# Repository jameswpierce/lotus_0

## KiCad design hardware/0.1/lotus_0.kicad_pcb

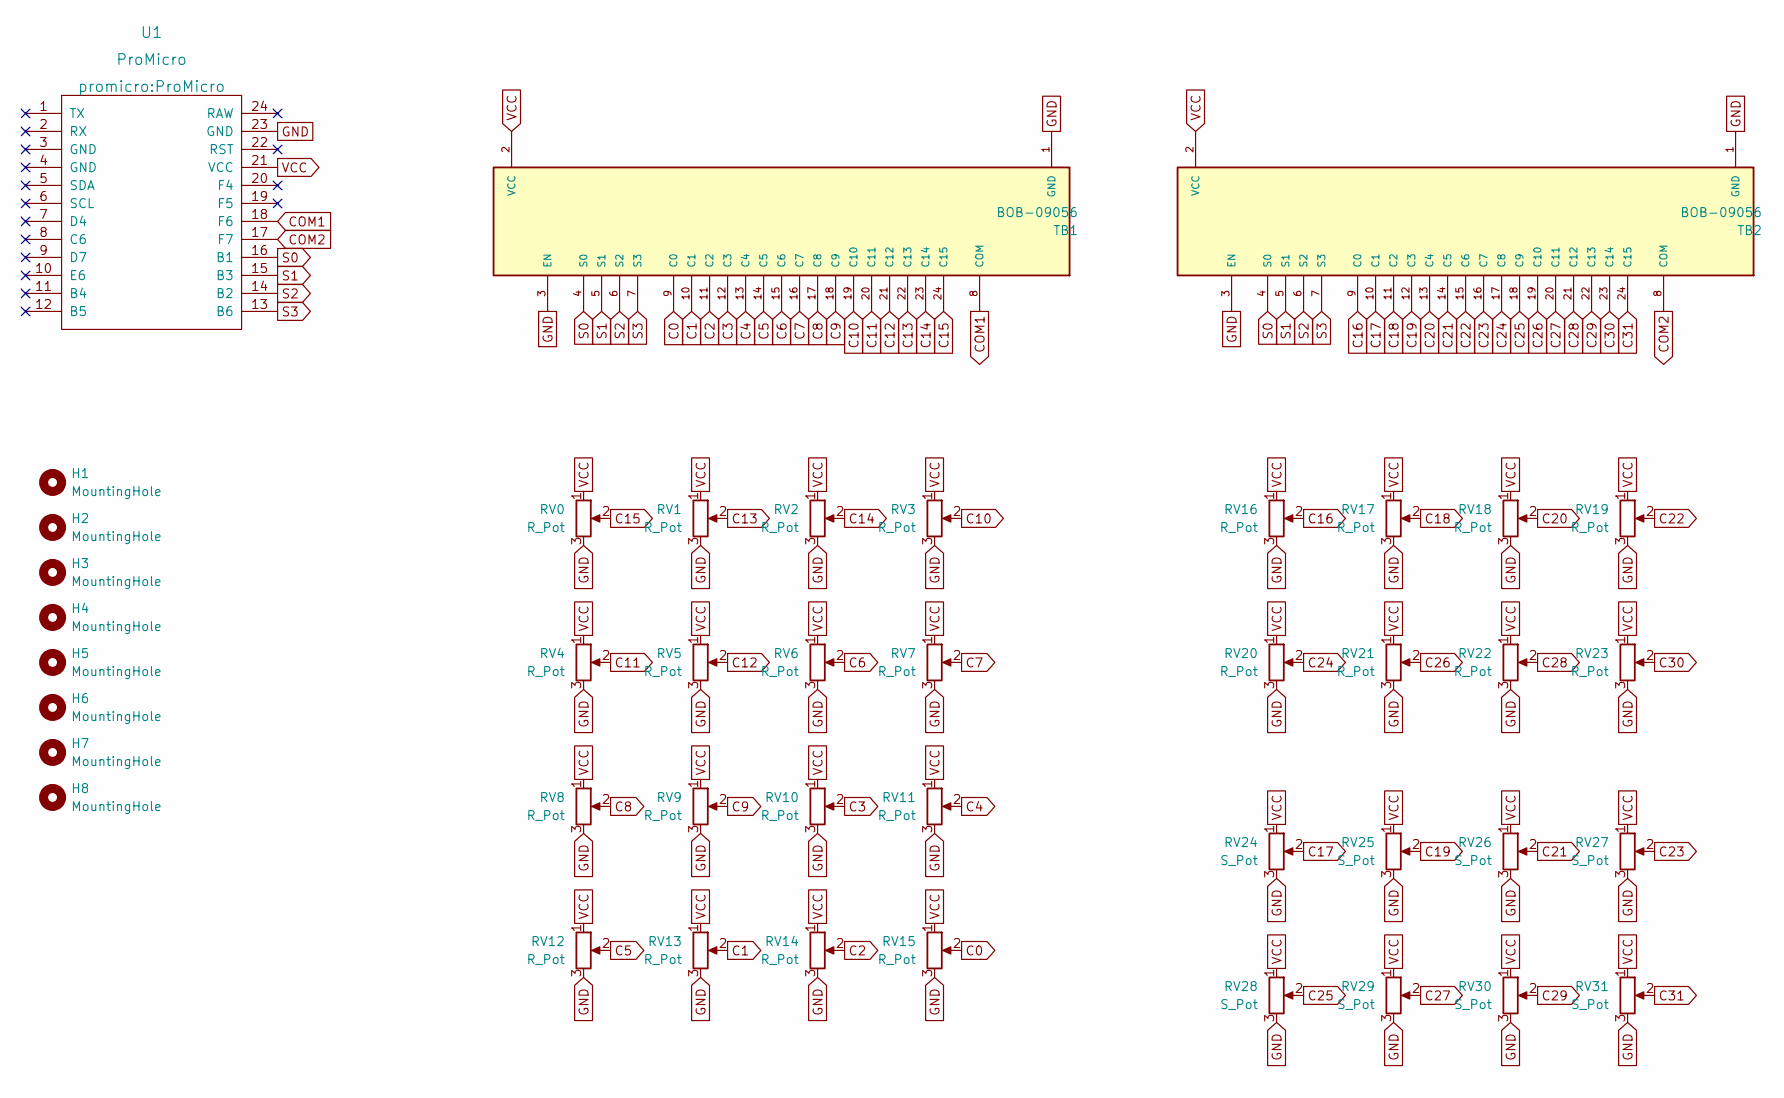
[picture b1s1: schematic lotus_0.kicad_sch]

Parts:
H1, H2, H3, H4, H5, H6, H7, H8: MountingHole; MountingHole_2.2mm_M2_DIN965_Pad
RV0, RV1, RV2, RV3, RV4, RV5, RV6, RV7, RV8, RV9, RV10, RV11, RV12, RV13, RV14, RV15, RV16, RV17, RV18, RV19, RV20, RV21, RV22, RV23: R_Pot; Potentiometer_Bourns_PTV09A-1_Single_Vertical
RV24, RV25, RV26, RV27, RV28, RV29, RV30, RV31: S_Pot; Potentiometer_Bourns_PTA6043_Single_Slide
TB1, TB2: BOB-09056; XDCR_BOB-09056; PARTREV N/A
U1: ProMicro

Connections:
C0: RV15.2, TB1.9 (C0)
C1: RV13.2, TB1.10 (C1)
C2: RV14.2, TB1.11 (C2)
C3: RV10.2, TB1.12 (C3)
C4: RV11.2, TB1.13 (C4)
C5: RV12.2, TB1.14 (C5)
C6: RV6.2, TB1.15 (C6)
C7: RV7.2, TB1.16 (C7)
C8: RV8.2, TB1.17 (C8)
C9: RV9.2, TB1.18 (C9)
C10: RV3.2, TB1.19 (C10)
C11: RV4.2, TB1.20 (C11)
C12: RV5.2, TB1.21 (C12)
C13: RV1.2, TB1.22 (C13)
C14: RV2.2, TB1.23 (C14)
C15: RV0.2, TB1.24 (C15)
C16: RV16.2, TB2.9 (C0)
C17: RV24.2, TB2.10 (C1)
C18: RV17.2, TB2.11 (C2)
C19: RV25.2, TB2.12 (C3)
C20: RV18.2, TB2.13 (C4)
C21: RV26.2, TB2.14 (C5)
C22: RV19.2, TB2.15 (C6)
C23: RV27.2, TB2.16 (C7)
C24: RV20.2, TB2.17 (C8)
C25: RV28.2, TB2.18 (C9)
C26: RV21.2, TB2.19 (C10)
C27: RV29.2, TB2.20 (C11)
C28: RV22.2, TB2.21 (C12)
C29: RV30.2, TB2.22 (C13)
C30: RV23.2, TB2.23 (C14)
C31: RV31.2, TB2.24 (C15)
COM1: TB1.8 (COM), U1.18 (F6)
COM2: TB2.8 (COM), U1.17 (F7)
GND: RV0.3, RV1.3, RV2.3, RV3.3, RV4.3, RV5.3, RV6.3, RV7.3, RV8.3, RV9.3, RV10.3, RV11.3, RV12.3, RV13.3, RV14.3, RV15.3, RV16.3, RV17.3, RV18.3, RV19.3, RV20.3, RV21.3, RV22.3, RV23.3, RV24.3, RV25.3, RV26.3, RV27.3, RV28.3, RV29.3, RV30.3, RV31.3, TB1.1 (GND), TB1.3 (EN), TB2.1 (GND), TB2.3 (EN), U1.23 (GND)
S0: TB1.4 (S0), TB2.4 (S0), U1.16 (B1)
S1: TB1.5 (S1), TB2.5 (S1), U1.15 (B3)
S2: TB1.6 (S2), TB2.6 (S2), U1.14 (B2)
S3: TB1.7 (S3), TB2.7 (S3), U1.13 (B6)
VCC: RV0.1, RV1.1, RV2.1, RV3.1, RV4.1, RV5.1, RV6.1, RV7.1, RV8.1, RV9.1, RV10.1, RV11.1, RV12.1, RV13.1, RV14.1, RV15.1, RV16.1, RV17.1, RV18.1, RV19.1, RV20.1, RV21.1, RV22.1, RV23.1, RV24.1, RV25.1, RV26.1, RV27.1, RV28.1, RV29.1, RV30.1, RV31.1, TB1.2 (VCC), TB2.2 (VCC), U1.21 (VCC)

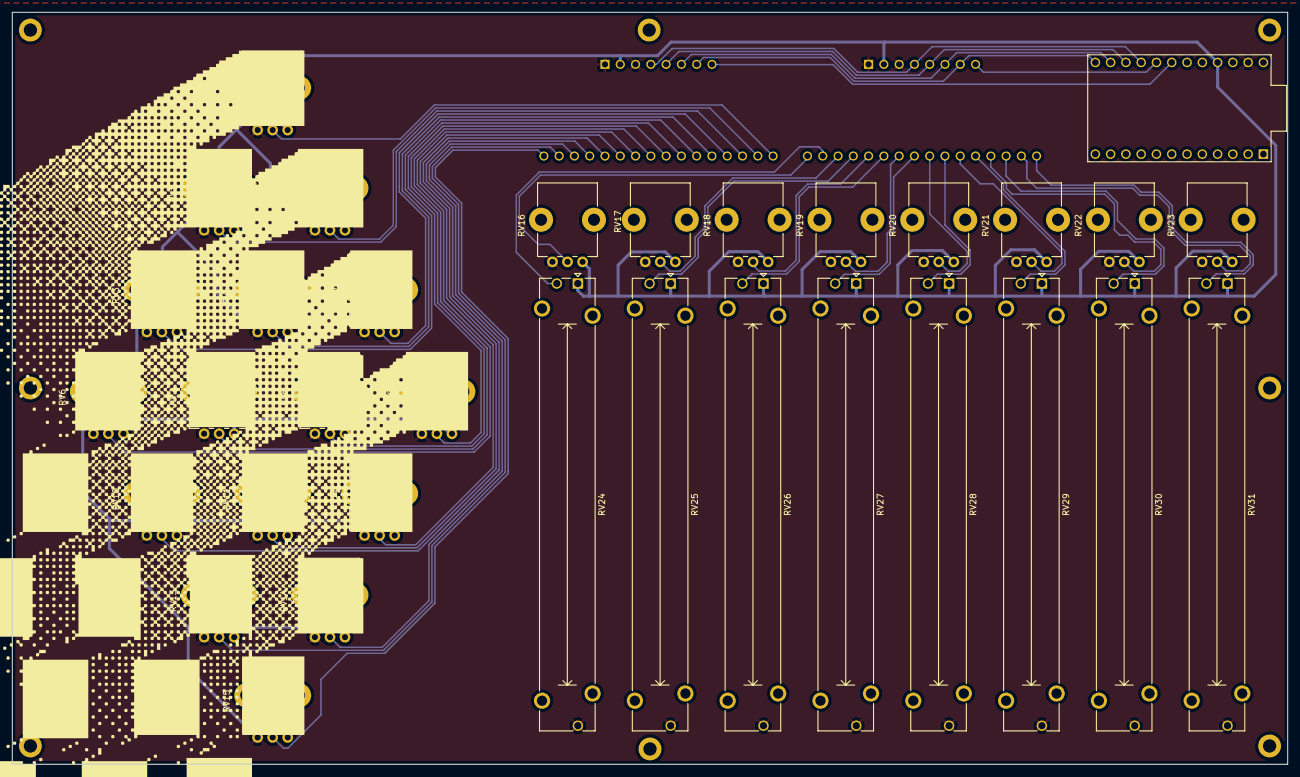
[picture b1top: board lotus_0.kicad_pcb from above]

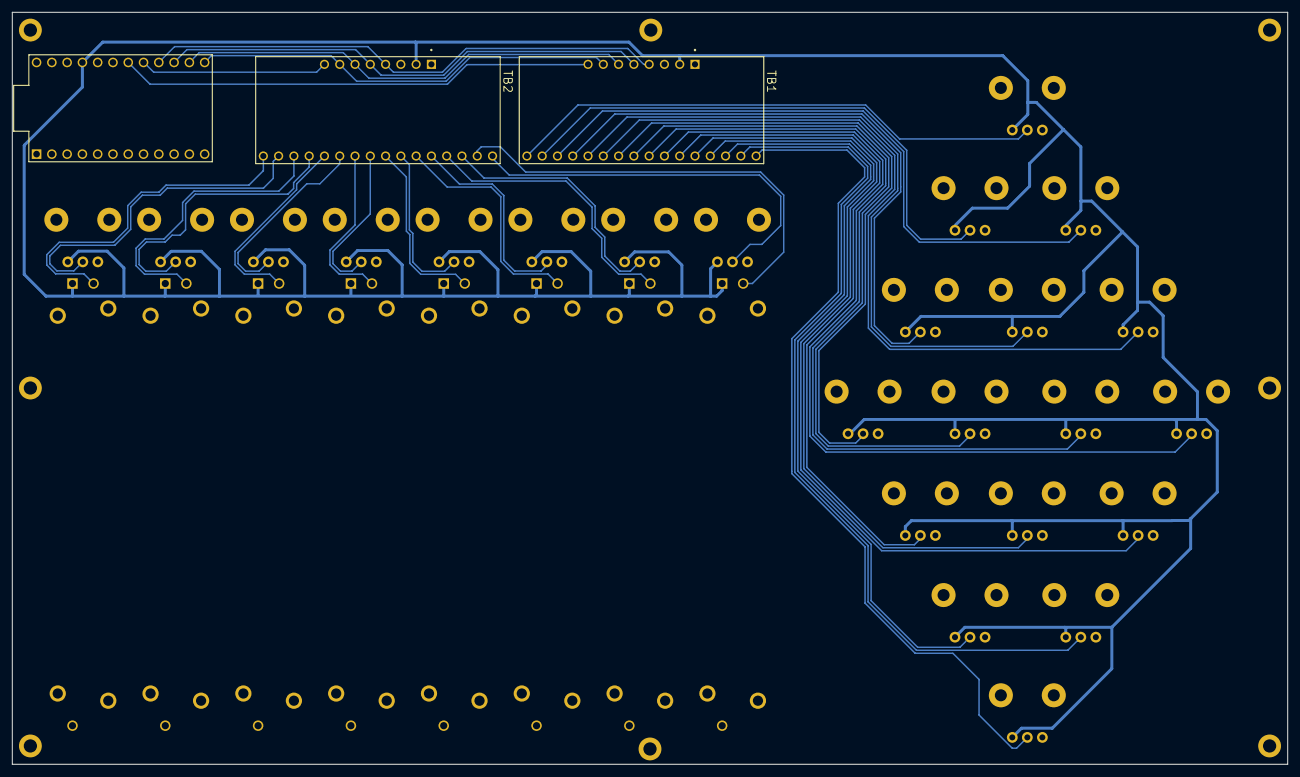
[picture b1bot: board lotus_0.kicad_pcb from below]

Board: 2 copper layers, 212.0 x 125.0 mm, 43 parts (3 on the bottom side), 40 nets.

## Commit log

2022-03-20 There falls no shadow where there shines no sun
2022-06-16 works
2022-06-17 move firmware to dir
2022-06-17 add kicad stuff
2022-06-21 add BOM
